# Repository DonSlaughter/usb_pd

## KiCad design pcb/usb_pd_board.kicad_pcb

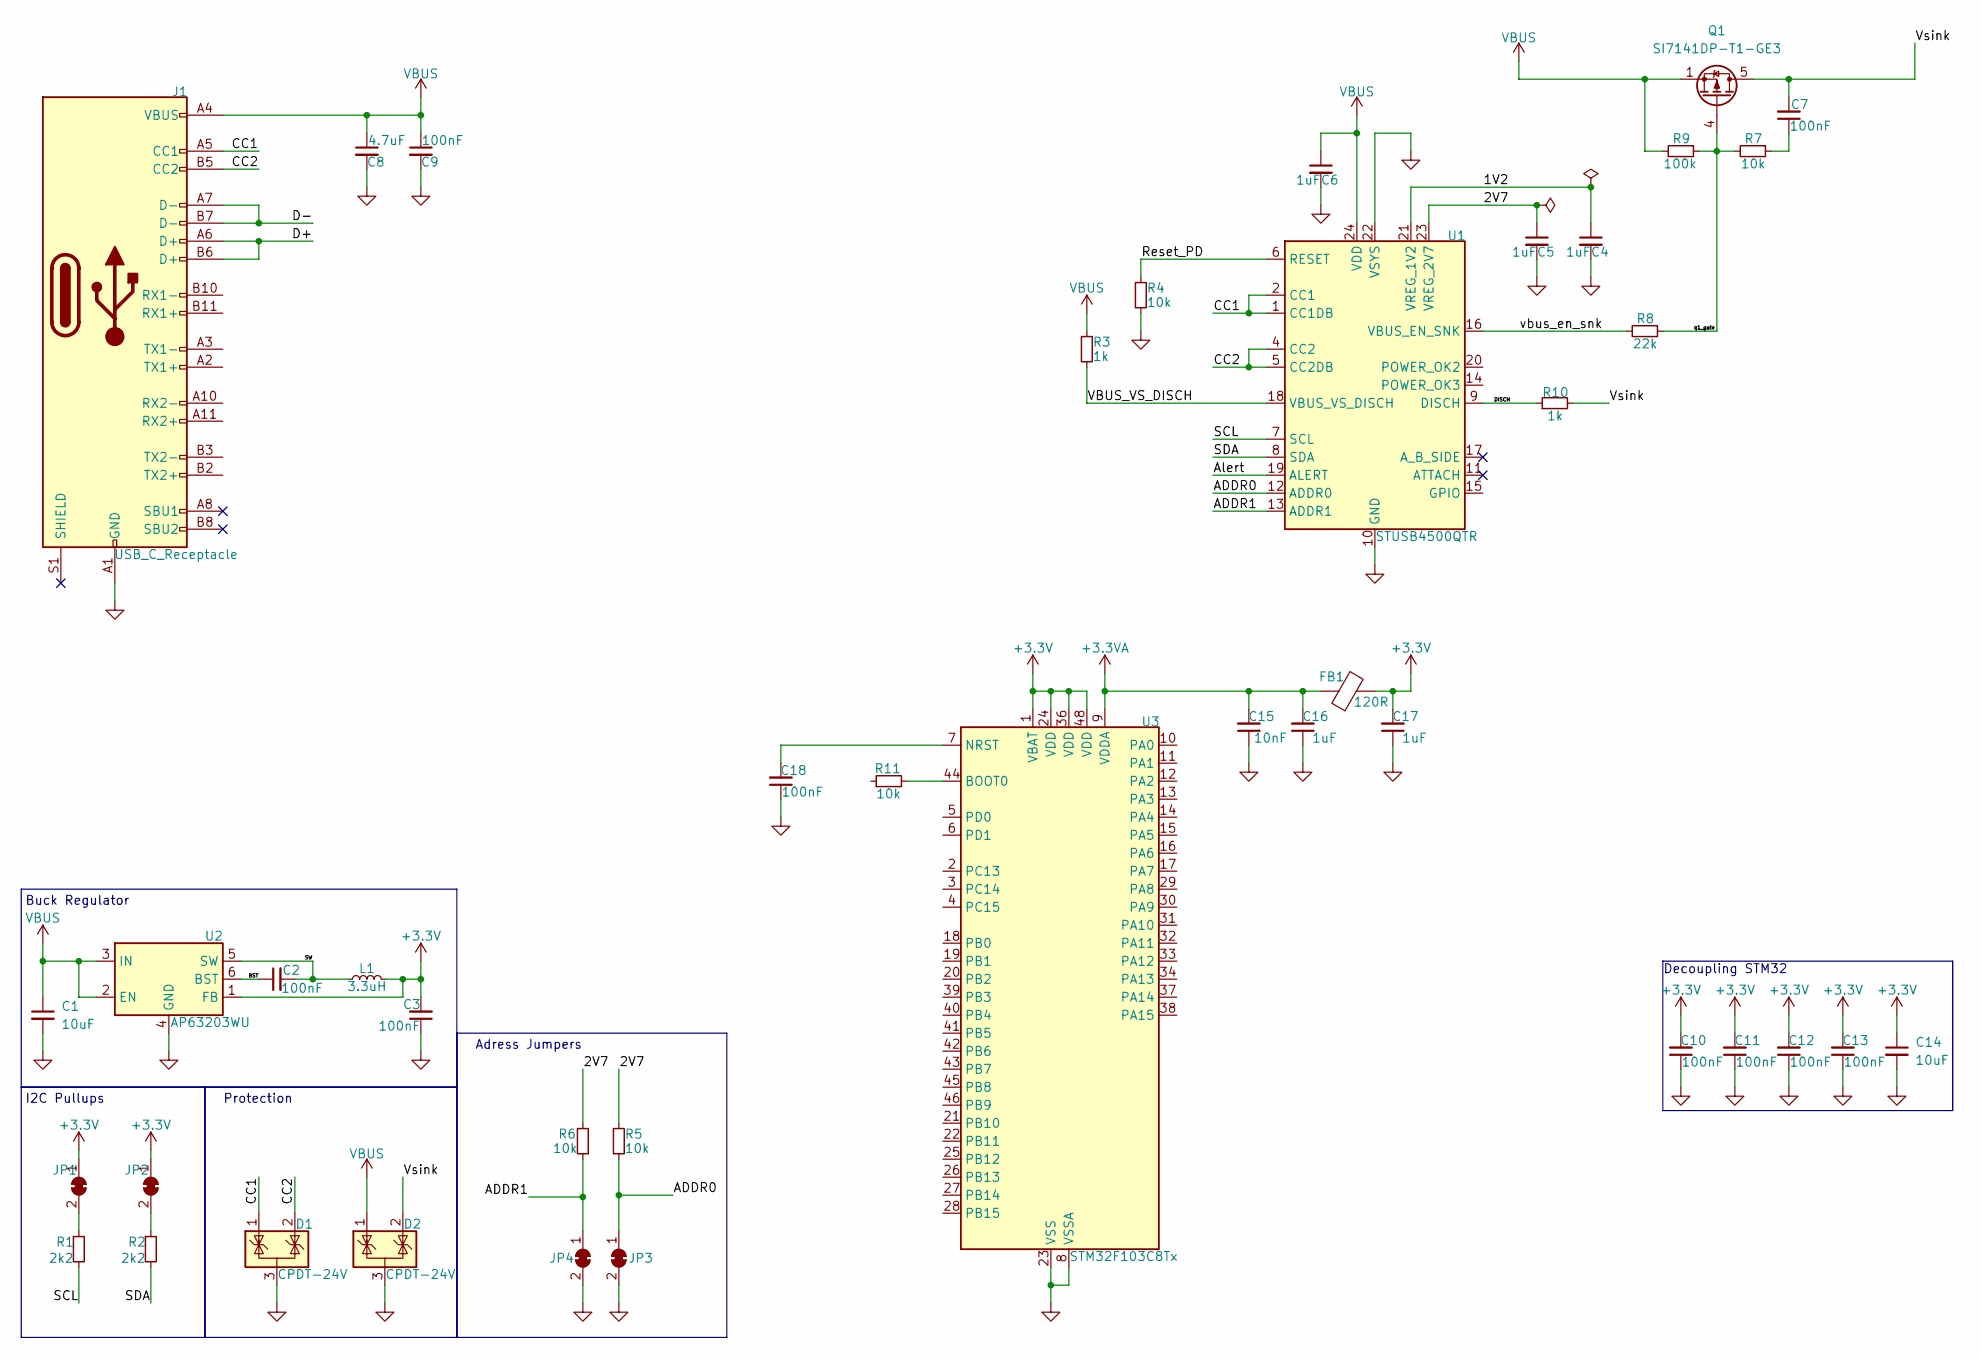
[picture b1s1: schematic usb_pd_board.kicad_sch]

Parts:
C1, C14: 10uF; C_0402_1005Metric_Pad0.74x0.62mm_HandSolder
C2, C3, C7, C9, C10, C11, C12, C13, C18: 100nF; C_0603_1608Metric_Pad1.08x0.95mm_HandSolder
C4, C5, C6, C16, C17: 1uF; C_0603_1608Metric_Pad1.08x0.95mm_HandSolder
C8: 4.7uF; C_0603_1608Metric_Pad1.08x0.95mm_HandSolder
C15: 10nF; C_0603_1608Metric_Pad1.08x0.95mm_HandSolder
D1, D2: CPDT-24V; SOT-23-3
FB1: 120R; L_0402_1005Metric_Pad0.77x0.64mm_HandSolder
J1: USB_C_Receptacle; USB_C_Receptacle_Amphenol_12401610E4-2A_CircularHoles
JP1, JP2, JP3, JP4: SolderJumper_2_Bridged; SolderJumper-2_P1.3mm_Bridged_RoundedPad1.0x1.5mm
L1: 3.3uH; L_0603_1608Metric_Pad1.05x0.95mm_HandSolder
Q1: SI7141DP-T1-GE3; Diodes_PowerDI3333-8
R1, R2: 2k2; R_0402_1005Metric_Pad0.72x0.64mm_HandSolder
R3, R10: 1k; R_0402_1005Metric_Pad0.72x0.64mm_HandSolder
R4, R5, R6, R7, R11: 10k; R_0402_1005Metric_Pad0.72x0.64mm_HandSolder
R8: 22k; R_0402_1005Metric_Pad0.72x0.64mm_HandSolder
R9: 100k; R_0402_1005Metric_Pad0.72x0.64mm_HandSolder
U1: STUSB4500QTR; QFN-24-1EP_4x4mm_P0.5mm_EP2.7x2.7mm
U2: AP63203WU; TSOT-23-6
U3: STM32F103C8Tx; LQFP-48_7x7mm_P0.5mm

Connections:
+3.3V: C3.2, C10.2, C11.2, C12.2, C13.2, C14.1, C17.2, FB1.2, JP1.1 (A), JP2.1 (A), L1.2, U2.1 (FB), U3.1 (VBAT), U3.24 (VDD), U3.36 (VDD), U3.48 (VDD)
+3.3VA: C15.2, C16.2, FB1.1, U3.9 (VDDA)
/1V2: C4.1, U1.21 (VREG_1V2)
/2V7: C5.1, R5.1, R6.1, U1.23 (VREG_2V7)
/ADDR0: JP3.1 (A), R5.2, U1.12 (ADDR0)
/ADDR1: JP4.1 (A), R6.2, U1.13 (ADDR1)
/Alert: U1.19 (ALERT)
/BST: C2.1, U2.6 (BST)
/CC1: D1.1 (K), J1.A5 (CC1), U1.1 (CC1DB), U1.2 (CC1)
/CC2: D1.2 (K), J1.B5 (CC2), U1.4 (CC2), U1.5 (CC2DB)
/D+: J1.A6 (D+), J1.B6 (D+)
/D-: J1.A7 (D-), J1.B7 (D-)
/DISCH: R10.1, U1.9 (DISCH)
/Reset_PD: R4.1, U1.6 (RESET)
/SCL: R1.2, U1.7 (SCL)
/SDA: R2.2, U1.8 (SDA)
/SW: C2.2, L1.1, U2.5 (SW)
/VBUS_VS_DISCH: R3.2, U1.18 (VBUS_VS_DISCH)
/Vsink: C7.2, D2.2 (K), Q1.5 (D), R10.2
/q1_gate: Q1.4 (G), R7.2, R8.1, R9.1
/vbus_en_snk: R8.2, U1.16 (VBUS_EN_SNK)
GND: C1.2, C3.1, C4.2, C5.2, C6.2, C8.2, C9.2, C10.1, C11.1, C12.1, C13.1, C14.2, C15.1, C16.1, C17.1, C18.1, D1.3 (A), D2.3 (A), J1.A1 (GND), J1.A12 (GND), J1.B1 (GND), J1.B12 (GND), JP3.2 (B), JP4.2 (B), R4.2, U1.10 (GND), U1.22 (VSYS), U1.25 (GND), U2.4 (GND), U3.8 (VSSA), U3.23 (VSS), U3.35 (VSS), U3.47 (VSS)
unnamed: C7.1, R7.1
unnamed: JP1.2 (B), R1.1
unnamed: JP2.2 (B), R2.1
unnamed: R11.2, U3.44 (BOOT0)
unnamed: C18.2, U3.7 (NRST)
VBUS: C1.1, C6.1, C8.1, C9.1, D2.1 (K), J1.A4 (VBUS), J1.A9 (VBUS), J1.B4 (VBUS), J1.B9 (VBUS), Q1.1 (S), Q1.2 (S), Q1.3 (S), R3.1, R9.2, U1.24 (VDD), U2.2 (EN), U2.3 (IN)

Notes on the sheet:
Buck Regulator
Adress Jumpers
Protection
I2C Pullups
Decoupling STM32

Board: 2 copper layers, 42 parts (0 on the bottom side), 27 nets, no tracks yet.

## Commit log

2023-07-28 gitignore added
2023-07-28 init
2023-08-02 datenblätter
